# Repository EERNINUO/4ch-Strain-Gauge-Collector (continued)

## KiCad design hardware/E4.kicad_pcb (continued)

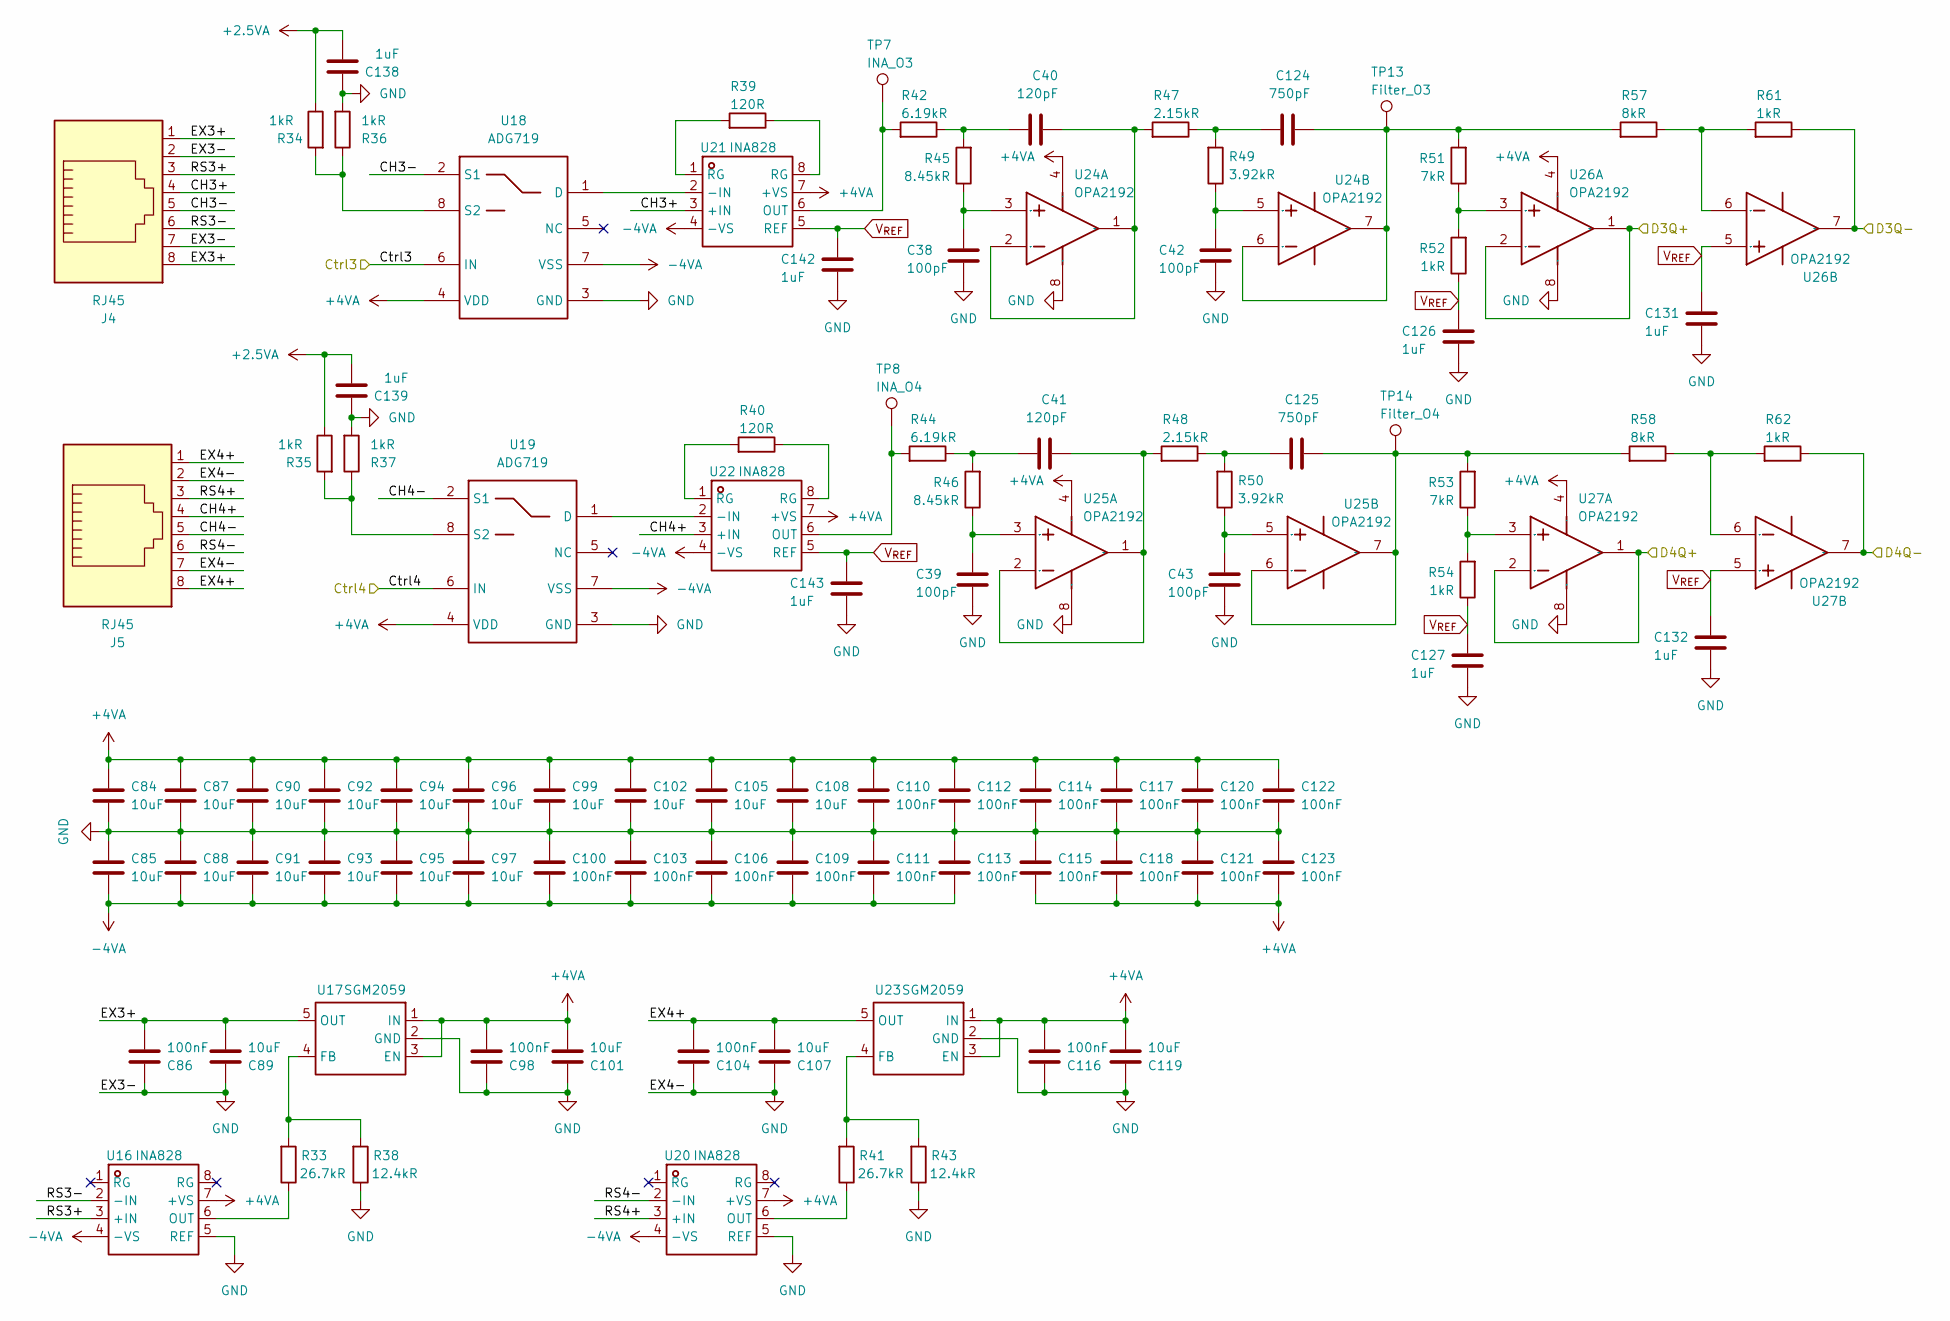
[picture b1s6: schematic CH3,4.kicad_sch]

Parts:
C38, C39, C42, C43: 100pF; C_0603_1608Metric
C40, C41: 120pF; C_0603_1608Metric
C84, C85, C87, C88, C89, C90, C91, C92, C93, C94, C95, C96, C97, C99, C101, C102, C105, C107, C108, C119: 10uF; C_0603_1608Metric
C86, C98, C100, C103, C104, C106, C109, C110, C111, C112, C113, C114, C115, C116, C117, C118, C120, C121, C122, C123: 100nF; C_0603_1608Metric
C124, C125: 750pF; C_0603_1608Metric
C126, C127, C131, C132, C138, C139, C142, C143: 1uF; C_0603_1608Metric
J4, J5: RJ45; RJ45_Amphenol_54602-x08_Horizontal
R33, R41: 26.7kR; R_0603_1608Metric
R34, R35, R36, R37, R52, R54, R61, R62: 1kR; R_0603_1608Metric
R38, R43: 12.4kR; R_0603_1608Metric
R39, R40: 120R; R_0603_1608Metric
R42, R44: 6.19kR; R_0603_1608Metric
R45, R46: 8.45kR; R_0603_1608Metric
R47, R48: 2.15kR; R_0603_1608Metric
R49, R50: 3.92kR; R_0603_1608Metric
R51, R53: 7kR; R_0603_1608Metric
R57, R58: 8kR; R_0603_1608Metric
TP7: INA_O3; TestPoint_Pad_D1.0mm
TP8: INA_O4; TestPoint_Pad_D1.0mm
TP13: Filter_O3; TestPoint_Pad_D1.0mm
TP14: Filter_O4; TestPoint_Pad_D1.0mm
U16, U20, U21, U22: INA828; SOIC-8_3.9x4.9mm_P1.27mm; Manufacturer Part INA828IDR; LCSC Part Name INA828IDR
U17, U23: SGM2059; SOT-23-5; Manufacturer Part SGM2059-ADJXN5G/TR; LCSC Part Name 300mA，低输入电压、超低噪声、高电源抑制比线性稳压器
U18, U19: ADG719; SOT-23-8; Manufacturer Part ADG619BRTZ-REEL7; LCSC Part Name CMOS单刀双掷开关
U24, U25, U26, U27: OPA2192; SOIC-8_3.9x4.9mm_P1.27mm; Manufacturer Part OPA2192IDR; LCSC Part Name OPA2192IDR

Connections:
+4VA: C84.1, C87.1, C90.1, C92.1, C94.1, C96.1, C98.2, C99.1, C101.2, C102.1, C105.1, C108.1, C110.2, C112.2, C114.2, C115.1, C116.2, C117.2, C118.1, C119.2, C120.2, C121.1, C122.2, C123.1, U16.7 (+VS), U17.1 (IN), U17.3 (EN), U18.4 (VDD), U19.4 (VDD), U20.7 (+VS), U21.7 (+VS), U22.7 (+VS), U23.1 (IN), U23.3 (EN), U24.4 (VSS), U25.4 (VSS), U26.4 (VSS), U27.4 (VSS); also elsewhere on the board
-4VA: C85.2, C88.2, C91.2, C93.2, C95.2, C97.2, C100.1, C103.1, C106.1, C109.1, C111.1, C113.1, U16.4 (-VS), U18.7 (VSS), U19.7 (VSS), U20.4 (-VS), U21.4 (-VS), U22.4 (-VS); also elsewhere on the board
/CH3,4/CH3+: J4.4, U21.3 (+IN)
/CH3,4/CH3-: J4.5, U18.2 (S1)
/CH3,4/CH4+: J5.4, U22.3 (+IN)
/CH3,4/CH4-: J5.5, U19.2 (S1)
/CH3,4/Ctrl3: U18.6 (IN); also elsewhere on the board
/CH3,4/Ctrl4: U19.6 (IN); also elsewhere on the board
/CH3,4/D3Q+: U26.1 (VOUTA), U26.2 (VINA-); also elsewhere on the board
/CH3,4/D3Q-: R61.1, U26.7 (VOUTB); also elsewhere on the board
/CH3,4/D4Q+: U27.1 (VOUTA), U27.2 (VINA-); also elsewhere on the board
/CH3,4/D4Q-: R62.1, U27.7 (VOUTB); also elsewhere on the board
/CH3,4/EX3+: C86.2, C89.2, J4.1, J4.8, U17.5 (OUT)
/CH3,4/EX4+: C104.2, C107.2, J5.1, J5.8, U23.5 (OUT)
/CH3,4/RS3+: J4.3, U16.3 (+IN)
/CH3,4/RS3-: J4.6, U16.2 (-IN)
/CH3,4/RS4+: J5.3, U20.3 (+IN)
/CH3,4/RS4-: J5.6, U20.2 (-IN)
GND: C38.2, C39.2, C42.2, C43.2, C84.2, C85.1, C86.1, C87.2, C88.1, C89.1, C90.2, C91.1, C92.2, C93.1, C94.2, C95.1, C96.2, C97.1, C98.1, C99.2, C100.2, C101.1, C102.2, C103.2, C104.1, C105.2, C106.2, C107.1, C108.2, C109.2, C110.1, C111.2, C112.1, C113.2, C114.1, C115.2, C116.1, C117.1, C118.2, C119.1, C120.1, C121.2, C122.1, C123.2, C126.2, C127.2, C131.2, C132.2, C138.1, C139.1, C142.2, C143.2, J4.2, J4.7, J5.2, J5.7, R36.2, R37.2, R38.1, R43.1, U16.5 (REF), U17.2 (GND), U18.3 (GND), U19.3 (GND), U20.5 (REF), U23.2 (GND), U24.8 (VDD), U25.8 (VDD), U26.8 (VDD), U27.8 (VDD); also elsewhere on the board
unnamed: C40.2, R42.1, R45.2
unnamed: C41.2, R44.1, R46.2
unnamed: C124.2, R47.1, R49.2
unnamed: C125.2, R48.1, R50.2
unnamed: R39.1, U21.8 (RG)
unnamed: R39.2, U21.1 (RG)
unnamed: R40.1, U22.8 (RG)
unnamed: R40.2, U22.1 (RG)
unnamed: R33.1, U16.6 (OUT)
unnamed: R33.2, R38.2, U17.4 (FB)
unnamed: U18.1 (D), U21.2 (-IN)
unnamed: R34.2, R36.1, U18.8 (S2)
unnamed: U19.1 (D), U22.2 (-IN)
unnamed: R35.2, R37.1, U19.8 (S2)
unnamed: R41.1, U20.6 (OUT)
unnamed: R42.2, TP7.1 (1_1), U21.6 (OUT)
unnamed: R44.2, TP8.1 (1_1), U22.6 (OUT)
unnamed: R41.2, R43.2, U23.4 (FB)
unnamed: C38.1, R45.1, U24.3 (VINA+)
unnamed: C40.1, R47.2, U24.1 (VOUTA), U24.2 (VINA-)
unnamed: C42.1, R49.1, U24.5 (VINB+)
unnamed: C124.1, R51.2, R57.2, TP13.1 (1_1), U24.6 (VINB-), U24.7 (VOUTB)
unnamed: C39.1, R46.1, U25.3 (VINA+)
unnamed: C41.1, R48.2, U25.1 (VOUTA), U25.2 (VINA-)
unnamed: C43.1, R50.1, U25.5 (VINB+)
unnamed: C125.1, R53.2, R58.2, TP14.1 (1_1), U25.6 (VINB-), U25.7 (VOUTB)
unnamed: R51.1, R52.2, U26.3 (VINA+)
unnamed: R57.1, R61.2, U26.6 (VINB-)
unnamed: R53.1, R54.2, U27.3 (VINA+)
unnamed: R58.1, R62.2, U27.6 (VINB-)

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
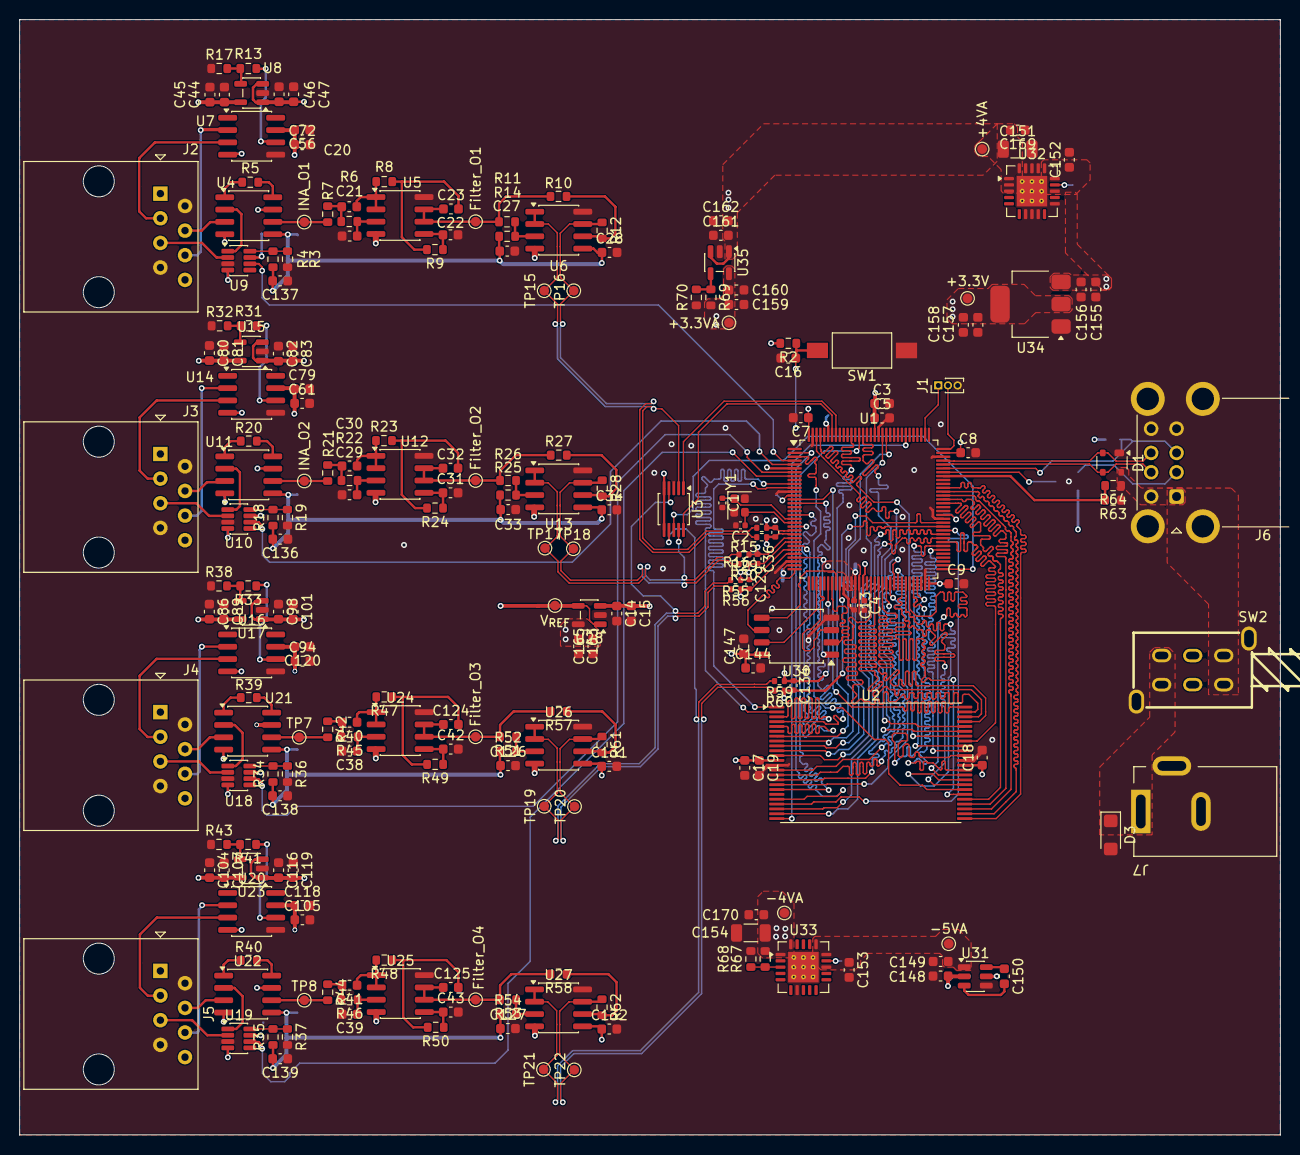
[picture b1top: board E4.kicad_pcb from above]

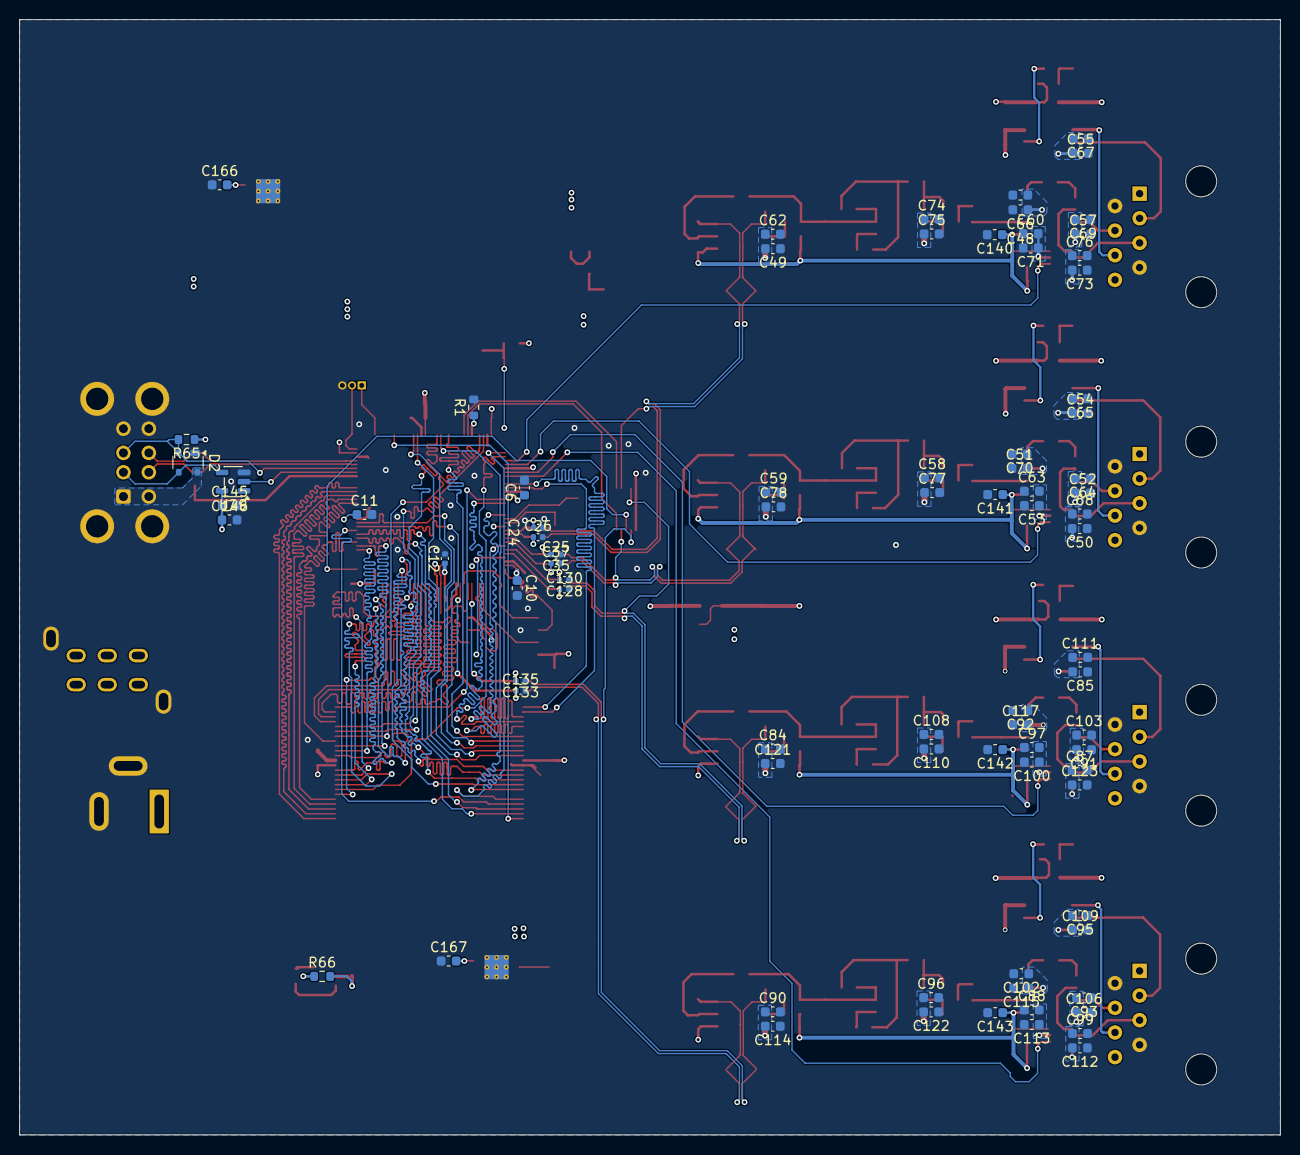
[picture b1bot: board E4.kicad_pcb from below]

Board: 4 copper layers, 130.0 x 115.0 mm, 308 parts (81 on the bottom side), 181 nets.

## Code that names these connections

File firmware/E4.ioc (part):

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Mcu.Name=STM32G473Q(B-C-E)Tx
Mcu.Package=LQFP128
Mcu.UserName=STM32G473QETx
PA0.Mode=IN1-Differential
PA0.Signal=ADC1_IN1
PA1.Mode=IN1-Differential
PA1.Signal=ADC1_IN2
PA10.Mode=Asynchronous
PA10.Signal=USART1_RX
PA11.Mode=Device
PA11.Signal=USB_DM
PA12.Mode=Device
PA12.Signal=USB_DP
PA13.Mode=Serial_Wire
PA13.Signal=SYS_JTMS-SWDIO
PA14.Mode=Serial_Wire
PA14.Signal=SYS_JTCK-SWCLK
PA2.Mode=Single Bank 1
PA2.Signal=QUADSPI1_BK1_NCS
PA3.Mode=Single Bank 1
PA3.Signal=QUADSPI1_CLK
PA6.Mode=Single Bank 1
PA6.Signal=QUADSPI1_BK1_IO3
PA7.Mode=Single Bank 1
PA7.Signal=QUADSPI1_BK1_IO2
PA8.GPIOParameters=GPIO_Label
PA8.GPIO_Label=USB_Check
PA8.Signal=GPXTI8
PA9.Mode=Asynchronous
PA9.Signal=USART1_TX
PB0.Mode=Single Bank 1
PB0.Signal=QUADSPI1_BK1_IO1
PB1.Mode=Single Bank 1
PB1.Signal=QUADSPI1_BK1_IO0
PB11.Mode=INP
PB11.Signal=COMP6_INP
PB2.Mode=IN11-Differential
PB2.Signal=ADC2_IN12
PB6.GPIOParameters=GPIO_Label
PB6.GPIO_Label=CTrig1
PB6.Signal=GPIO_Output
PB7.GPIOParameters=GPIO_Label
PB7.GPIO_Label=CTrig0
PB7.Signal=GPIO_Output
PC0.Mode=IN6-Differential
PC0.Signal=ADC2_IN6
PC1.Mode=IN6-Differential
PC1.Signal=ADC2_IN7
PC13.GPIOParameters=GPIO_Label
PC13.GPIO_Label=Ctrl3
PC13.Signal=GPIO_Output
PC14-OSC32_IN.GPIOParameters=GPIO_Label
PC14-OSC32_IN.GPIO_Label=Ctrl4
PC14-OSC32_IN.Signal=GPIO_Output
PC2.Mode=IN8-Differential
PC2.Signal=ADC1_IN8
PC3.Mode=IN8-Differential
PC3.Signal=ADC1_IN9
PC5.Mode=IN11-Differential
PC5.Signal=ADC2_IN11
PD0.Signal=FMC_D2_DA2
PD1.Signal=FMC_D3_DA3
PD10.Signal=FMC_D15_DA15
PD11.Signal=FMC_A16_CLE
PD12.Signal=FMC_A17_ALE
PD13.Signal=FMC_A18
PD14.Signal=FMC_D0_DA0
PD15.Signal=FMC_D1_DA1
PD4.Signal=FMC_NOE
PD5.Signal=FMC_NWE
PD7.Mode=NorPsramChipSelect1_1
PD7.Signal=FMC_NE1
PD8.Signal=FMC_D13_DA13
PD9.Signal=FMC_D14_DA14
PE10.Signal=FMC_D7_DA7
PE11.Signal=FMC_D8_DA8
PE12.Signal=FMC_D9_DA9
PE13.Signal=FMC_D10_DA10
PE14.Signal=FMC_D11_DA11
PE15.Signal=FMC_D12_DA12
PE3.Signal=FMC_A19
PE4.Signal=FMC_A20
PE5.GPIOParameters=GPIO_Label
PE5.GPIO_Label=Ctrl1
PE5.Signal=GPIO_Output
PE6.GPIOParameters=GPIO_Label
PE6.GPIO_Label=Ctrl2
PE6.Signal=GPIO_Output
PE7.Signal=FMC_D4_DA4
PE8.Signal=FMC_D5_DA5
PE9.Signal=FMC_D6_DA6
PF0-OSC_IN.Mode=HSE-External-Oscillator
PF0-OSC_IN.Signal=RCC_OSC_IN
PF1-OSC_OUT.Mode=HSE-External-Oscillator
PF1-OSC_OUT.Signal=RCC_OSC_OUT
PF10.Signal=FMC_A0
PF12.Signal=FMC_A6
PF13.Signal=FMC_A7
PF14.Signal=FMC_A8
PF15.Signal=FMC_A9
PF2.Signal=FMC_A2
PF3.Signal=FMC_A3
PF4.Signal=FMC_A4
PF5.Signal=FMC_A5
PF7.Signal=FMC_A1
PG0.Signal=FMC_A10
PG1.Signal=FMC_A11
PG2.Signal=FMC_A12
PG3.Signal=FMC_A13
PG4.Signal=FMC_A14
PG5.Signal=FMC_A15
RCC.HSE_VALUE=24000000
RCC.SYSCLKFreq_VALUE=144000000
RCC.SYSCLKSource=RCC_SYSCLKSOURCE_PLLCLK
board=custom

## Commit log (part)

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2026-05-26 创建仓库
2026-05-28 feat：绘制元件库
2026-05-28 feat：MCU最小系统原理图设计；SRAM原理图设计
2026-05-28 feat：MCU引脚初步分配（ADC、QSPI、SRAM、电平触发、USB、USART、最小系统）
2026-05-29 docs：完成硬件架构文档
2026-05-29 docs：硬件设计文档-MCU最小系统
2026-06-01 feat：修复README显示问题
2026-06-01 docs：仪表放大器设计
2026-06-01 simulation：仪表放大器部分
2026-06-02 simulation：滤波器部分
2026-06-02 simulation：单端转差分部分
2026-06-02 docs：滤波器设计；差分转单端设计
2026-06-02 feat：仪表放大器、滤波器原理图
2026-06-02 feat：差分转单端原理图
2026-06-02 docs：更换仪表放大器-模拟开关选型
2026-06-02 feat：远程感测原理图；多路通道
2026-06-02 docs：补充原理图
2026-06-03 feat：输入滤波原理图
2026-06-03 feat：电平触发原理图
2026-06-03 feat：QSPI原理图
2026-06-03 feat：电源原理图
2026-06-03 docs：外部触发、存储扩展、电源设计；PCB布局布线指南
2026-06-04 feat：模拟前端布线，单片机/SRAM布线
2026-06-04 feat：电源部分
2026-06-04 feat：总体连接
2026-06-04 feat：完成BOM表
2026-06-04 feat：CubeMX配置
2026-06-04 docs：软件设计文档
2026-06-05 docs：报告整理
2026-06-05 feat：整理设计文件
2026-06-05 simulation：整理设计文件
